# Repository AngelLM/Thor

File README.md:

<h1 align="center">
 <a href="http://thor.angel-lm.com">
    <picture>
      <source height="80" media="(prefers-color-scheme: dark)" srcset="doc/logo_dark.svg">
      
    </picture>
  </a>

 <br>

</h1>
<p align="center">
 <em><b>Thor</b> is an open source, 3D printed, 6 degrees of freedom robotic arm. Designed to be affordable and accessible, Thor is ideal for educational settings, makers, and robotics enthusiasts. With a height of 625mm it has the capacity to lift up to 750g. Its yaw-roll-roll-yaw-roll-yaw configuration is common in industrial manipulators.</em>
</p>

## ✨ Key Features

- 🧩 **Born Open Source**: Designed using open source software such as FreeCAD, KiCAD, GRBL, RRF and ROS.
- 🕊️ **Released Open Source**: All source files published under CC-BY-SA-4.0 license.
- 💰 **Low Cost**: Hardware cost below 350€.
- 📚  **Suitable for education**: Perfect for robotics courses in schools and universities, there are already success cases!
- 🧰 **G-code Controlled**: Uses the same language as 3d printers and CNCs to move.
- 🐳 **ROS2 Integration**: Available implementation using Docker for flexibility.

## 📦 Repository Structure
- `freecad-src` – Source files of 3D models created with FreeCAD
- `mods` – Modified models and improvements to standard models
- `stl` – Printable STL files
- `step` – STEP files

## 🔗 Related Repositories
- [**Thor-ROS**](https://github.com/AngelLM/Thor-ROS): ROS2 & Moveit2 configuration files and packages to work with Thor.
- [**ThorControlPCB**](https://github.com/AngelLM/ThorControlPCB): Source & manufacture files of Arduino Mega shield designed to control Thor.
- [**Asgard**](https://github.com/AngelLM/Asgard): Control software for thor motors with a simple interface.

## 🚀 Getting Started

1. **Read the Documentation**: Comprehensive guides on printing, assembly, electronics, and firmware are available at [thor.angel-lm.com/documentation](http://thor.angel-lm.com/documentation/).
2. **Print the Parts**: Use the STL files in this repository.
3. **Get the Hardware**: Take a look to the [Bill of Materials](http://thor.angel-lm.com/documentation/bom/).
4. **Assemble the Robot**: See [here](http://thor.angel-lm.com/documentation/assembly/) for assembly videos and interactive instructions. 
5. **Assemble & Setup the Electronics**: The [Wiring & Setup](http://thor.angel-lm.com/documentation/electronics/) guide will help you prepare your electronic board and make the hardware connections. 
6. **Install the Firmware**: Depending on which electronics you have chosen, you will have to perform a different firmware configuration. [This page](http://thor.angel-lm.com/documentation/firmware/) explains the steps to follow.
7. **Control the Robot**: Use Asgard to move the robot. [Here](http://thor.angel-lm.com/documentation/control-software/) is how to do it.

## 🧠 Technical Specifications

- **Degrees of Freedom**: 6 (yaw-roll-roll-yaw-roll-yaw).
- **Height Stretched**: 625mm (without end effector).
- **Payload Capacity**: 750g max (including end effector weight).
- **Motors**: Stepper motors.
- **Electronics**: DIY PCB or commercial boards.
- **Transmission**: 3D printed gears, GT2 pulleys and belts.
- **Software**: FreeCAD, KiCAD, GRBL, RRF, ROS2.

## 📚 Additional Resources

- 🌐 **Official Website**: [thor.angel-lm.com](http://thor.angel-lm.com/)
- ❓ **Frequently Asked Questions**: [FAQ](http://thor.angel-lm.com/faq/)
- 💬 **Thor Community Forums**: [Thor Forums](http://thor.angel-lm.com/forums/)
- 💬 **Thor Discord Server**: [Thor Robot Community](https://discord.com/invite/a5dSVqSUK5)

## 🤝 Contributing

Contributions are welcome! If you'd like to improve Thor — whether it's design, documentation, or code — feel free to open an [Issue](https://github.com/AngelLM/Thor/issues) or submit a Pull Request.

## 📜 License

Thor is licensed under the [Creative Commons Attribution-ShareAlike 4.0 International License](https://creativecommons.org/licenses/by-sa/4.0/legalcode). You’re free to use, modify, and distribute this project under its terms.

## 🎥 Videos

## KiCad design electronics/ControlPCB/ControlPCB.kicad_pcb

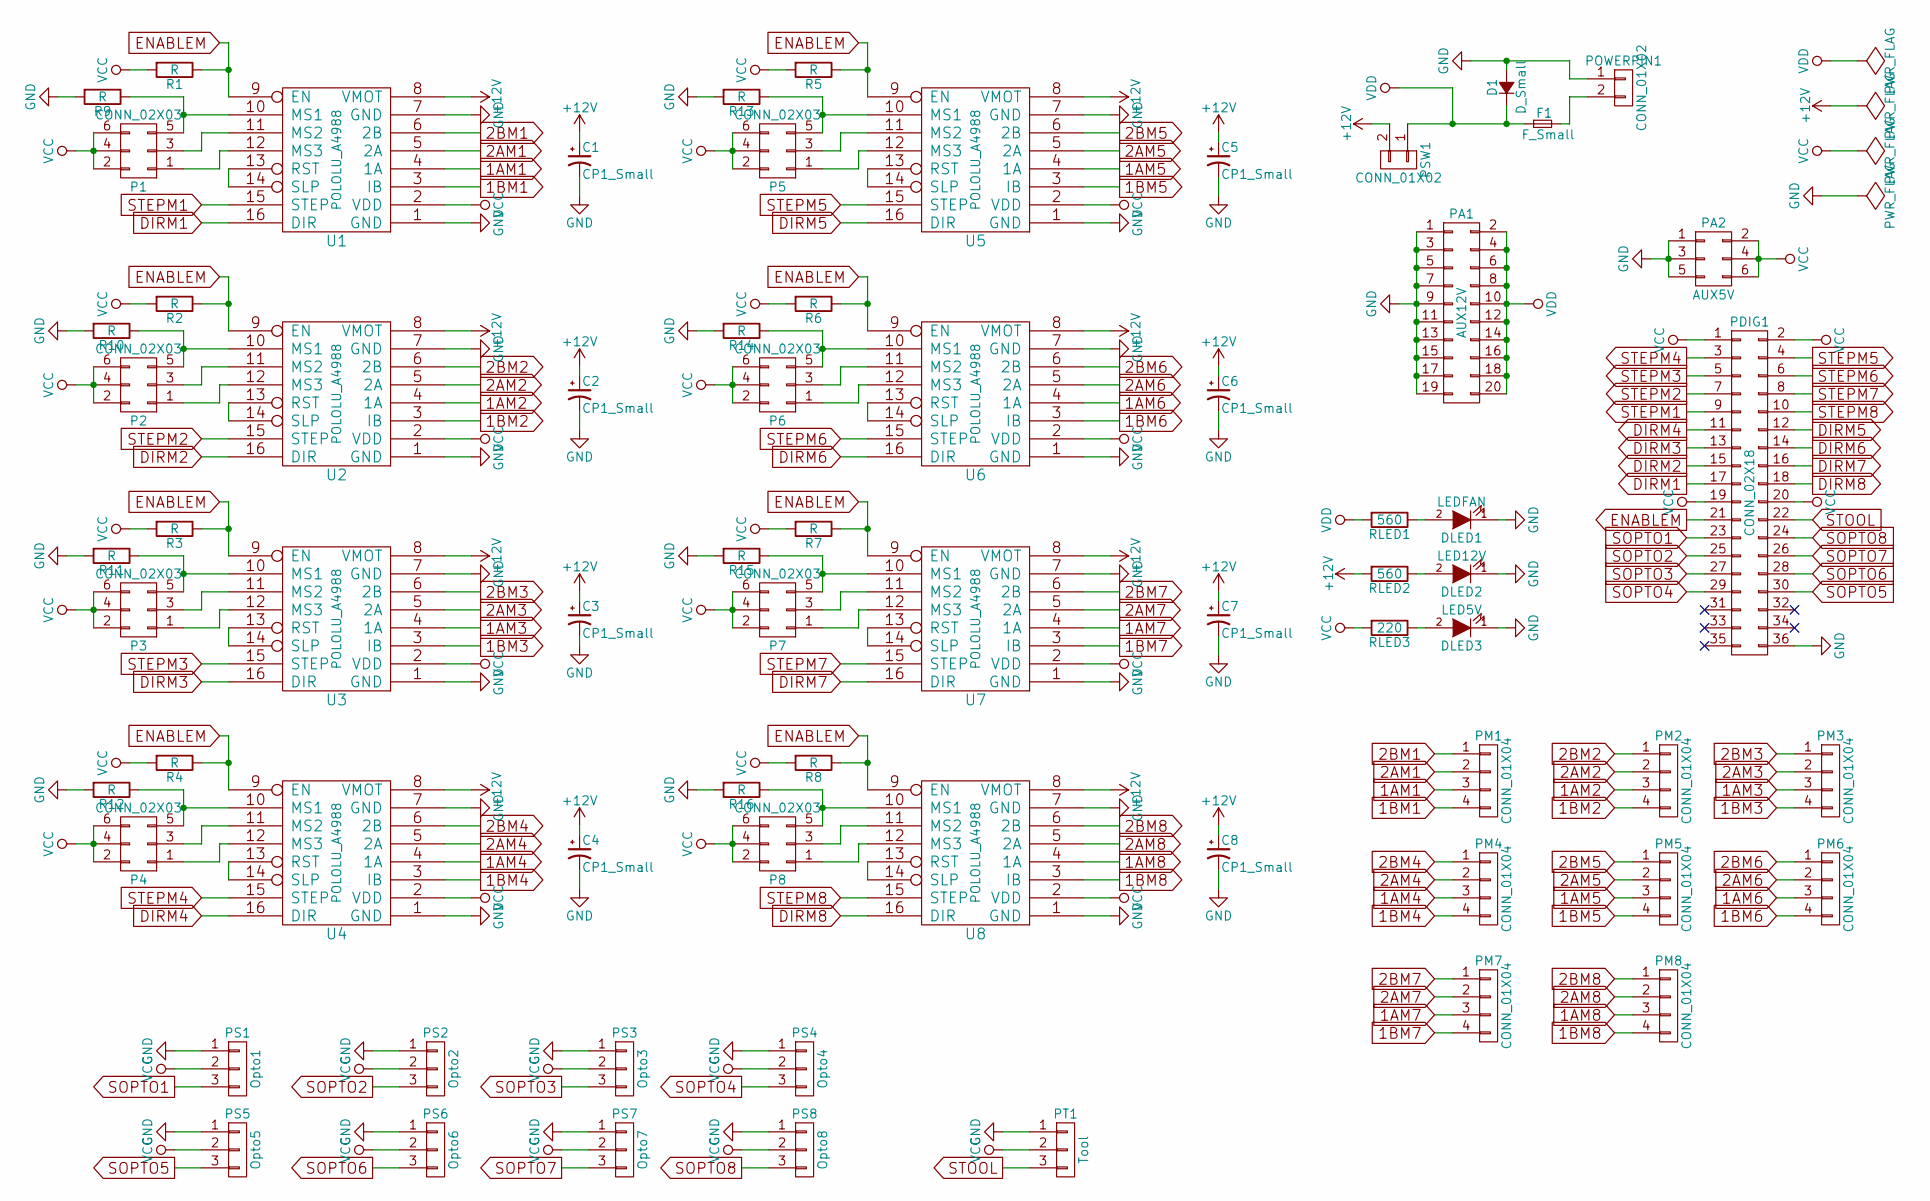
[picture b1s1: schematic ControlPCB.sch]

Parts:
C1, C2, C3, C4, C5, C6, C7, C8: CP1_Small; c_elec_6.3x5.7
D1: D_Small; Diode_DO-35_SOD27_Horizontal_RM10
DLED1: LEDFAN; LED_1206
DLED2: LED12V; LED_1206
DLED3: LED5V; LED_1206
F1: F_Small; BladeFuse-CarType
P1, P2, P3, P4, P5, P6, P7, P8: CONN_02X03; Pin_Header_Straight_2x03
PA1: AUX12V; Pin_Header_Straight_2x10
PA2: AUX5V; Pin_Header_Straight_2x03
PDIG1: CONN_02X18; Pin_Header_Straight_2x18
PM1, PM2, PM3, PM4, PM5, PM6, PM7, PM8: CONN_01X04; Pin_Header_Straight_1x04
POWERPIN1: CONN_01X02; Pin_Header_Straight_1x02
PS1: Opto1; Pin_Header_Straight_1x03
PS2: Opto2; Pin_Header_Straight_1x03
PS3: Opto3; Pin_Header_Straight_1x03
PS4: Opto4; Pin_Header_Straight_1x03
PS5: Opto5; Pin_Header_Straight_1x03
PS6: Opto6; Pin_Header_Straight_1x03
PS7: Opto7; Pin_Header_Straight_1x03
PS8: Opto8; Pin_Header_Straight_1x03
PSW1: CONN_01X02; Pin_Header_Straight_1x02
PT1: Tool; Pin_Header_Straight_1x03
R1, R2, R3, R4, R5, R6, R7, R8, R9, R10, R11, R12, R13, R14, R15, R16: R; R_1206_HandSoldering
RLED1, RLED2: 560; R_1206_HandSoldering
RLED3: 220; R_1206_HandSoldering
U1, U2, U3, U4, U5, U6, U7, U8: POLOLU_A4988; SWDIP8_.6W

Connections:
1AM1: PM1.3, U1.4 (1A)
1AM2: PM2.3, U2.4 (1A)
1AM3: PM3.3, U3.4 (1A)
1AM4: PM4.3, U4.4 (1A)
1AM5: PM5.3, U5.4 (1A)
1AM6: PM6.3, U6.4 (1A)
1AM7: PM7.3, U7.4 (1A)
1AM8: PM8.3, U8.4 (1A)
1BM1: PM1.4, U1.3 (IB)
1BM2: PM2.4, U2.3 (IB)
1BM3: PM3.4, U3.3 (IB)
1BM4: PM4.4, U4.3 (IB)
1BM5: PM5.4, U5.3 (IB)
1BM6: PM6.4, U6.3 (IB)
1BM7: PM7.4, U7.3 (IB)
1BM8: PM8.4, U8.3 (IB)
2AM1: PM1.2, U1.5 (2A)
2AM2: PM2.2, U2.5 (2A)
2AM3: PM3.2, U3.5 (2A)
2AM4: PM4.2, U4.5 (2A)
2AM5: PM5.2, U5.5 (2A)
2AM6: PM6.2, U6.5 (2A)
2AM7: PM7.2, U7.5 (2A)
2AM8: PM8.2, U8.5 (2A)
2BM1: PM1.1, U1.6 (2B)
2BM2: PM2.1, U2.6 (2B)
2BM3: PM3.1, U3.6 (2B)
2BM4: PM4.1, U4.6 (2B)
2BM5: PM5.1, U5.6 (2B)
2BM6: PM6.1, U6.6 (2B)
2BM7: PM7.1, U7.6 (2B)
2BM8: PM8.1, U8.6 (2B)
+12V: C1.1, C2.1, C3.1, C4.1, C5.1, C6.1, C7.1, C8.1, PSW1.2, RLED2.2, U1.8 (VMOT), U2.8 (VMOT), U3.8 (VMOT), U4.8 (VMOT), U5.8 (VMOT), U6.8 (VMOT), U7.8 (VMOT), U8.8 (VMOT)
DIRM1: PDIG1.17, U1.16 (DIR)
DIRM2: PDIG1.15, U2.16 (DIR)
DIRM3: PDIG1.13, U3.16 (DIR)
DIRM4: PDIG1.11, U4.16 (DIR)
DIRM5: PDIG1.12, U5.16 (DIR)
DIRM6: PDIG1.14, U6.16 (DIR)
DIRM7: PDIG1.16, U7.16 (DIR)
DIRM8: PDIG1.18, U8.16 (DIR)
ENABLEM: PDIG1.21, R1.1, R2.1, R3.1, R4.1, R5.1, R6.1, R7.1, R8.1, U1.9 (EN), U2.9 (EN), U3.9 (EN), U4.9 (EN), U5.9 (EN), U6.9 (EN), U7.9 (EN), U8.9 (EN)
GND: C1.2, C2.2, C3.2, C4.2, C5.2, C6.2, C7.2, C8.2, D1.2 (A), DLED1.1 (K), DLED2.1 (K), DLED3.1 (K), PA1.1, PA1.3, PA1.5, PA1.7, PA1.9, PA1.11, PA1.13, PA1.15, PA1.17, PA1.19, PA2.1, PA2.3, PA2.5, PDIG1.36, POWERPIN1.1, PS1.1, PS2.1, PS3.1, PS4.1, PS5.1, PS6.1, PS7.1, PS8.1, PT1.1, R9.2, R10.2, R11.2, R12.2, R13.2, R14.2, R15.2, R16.2, U1.1 (GND), U1.7 (GND), U2.1 (GND), U2.7 (GND), U3.1 (GND), U3.7 (GND), U4.1 (GND), U4.7 (GND), U5.1 (GND), U5.7 (GND), U6.1 (GND), U6.7 (GND), U7.1 (GND), U7.7 (GND), U8.1 (GND), U8.7 (GND)
unnamed: DLED1.2 (A), RLED1.1
unnamed: DLED2.2 (A), RLED2.1
unnamed: DLED3.2 (A), RLED3.1
unnamed: F1.2, POWERPIN1.2
unnamed: P1.1, U1.12 (MS3)
unnamed: P1.3, U1.11 (MS2)
unnamed: P1.5, R9.1, U1.10 (MS1)
unnamed: P2.1, U2.12 (MS3)
unnamed: P2.3, U2.11 (MS2)
unnamed: P2.5, R10.1, U2.10 (MS1)
unnamed: P3.1, U3.12 (MS3)
unnamed: P3.3, U3.11 (MS2)
unnamed: P3.5, R11.1, U3.10 (MS1)
unnamed: P4.1, U4.12 (MS3)
unnamed: P4.3, U4.11 (MS2)
unnamed: P4.5, R12.1, U4.10 (MS1)
unnamed: P5.1, U5.12 (MS3)
unnamed: P5.3, U5.11 (MS2)
unnamed: P5.5, R13.1, U5.10 (MS1)
unnamed: P6.1, U6.12 (MS3)
unnamed: P6.3, U6.11 (MS2)
unnamed: P6.5, R14.1, U6.10 (MS1)
unnamed: P7.1, U7.12 (MS3)
unnamed: P7.3, U7.11 (MS2)
unnamed: P7.5, R15.1, U7.10 (MS1)
unnamed: P8.1, U8.12 (MS3)
unnamed: P8.3, U8.11 (MS2)
unnamed: P8.5, R16.1, U8.10 (MS1)
unnamed: U1.13 (RST), U1.14 (SLP)
unnamed: U2.13 (RST), U2.14 (SLP)
unnamed: U3.13 (RST), U3.14 (SLP)
unnamed: U4.13 (RST), U4.14 (SLP)
unnamed: U5.13 (RST), U5.14 (SLP)
unnamed: U6.13 (RST), U6.14 (SLP)
unnamed: U7.13 (RST), U7.14 (SLP)
unnamed: U8.13 (RST), U8.14 (SLP)
SOPTO1: PDIG1.23, PS1.3
SOPTO2: PDIG1.25, PS2.3
SOPTO3: PDIG1.27, PS3.3
SOPTO4: PDIG1.29, PS4.3
SOPTO5: PDIG1.30, PS5.3
SOPTO6: PDIG1.28, PS6.3
SOPTO7: PDIG1.26, PS7.3
SOPTO8: PDIG1.24, PS8.3
STEPM1: PDIG1.9, U1.15 (STEP)
STEPM2: PDIG1.7, U2.15 (STEP)
STEPM3: PDIG1.5, U3.15 (STEP)
STEPM4: PDIG1.3, U4.15 (STEP)
STEPM5: PDIG1.4, U5.15 (STEP)
STEPM6: PDIG1.6, U6.15 (STEP)
STEPM7: PDIG1.8, U7.15 (STEP)
STEPM8: PDIG1.10, U8.15 (STEP)
STOOL: PDIG1.22, PT1.3
VCC: P1.2, P1.4, P1.6, P2.2, P2.4, P2.6, P3.2, P3.4, P3.6, P4.2, P4.4, P4.6, P5.2, P5.4, P5.6, P6.2, P6.4, P6.6, P7.2, P7.4, P7.6, P8.2, P8.4, P8.6, PA2.2, PA2.4, PA2.6, PDIG1.1, PDIG1.2, PDIG1.19, PDIG1.20, PS1.2, PS2.2, PS3.2, PS4.2, PS5.2, PS6.2, PS7.2, PS8.2, PT1.2, R1.2, R2.2, R3.2, R4.2, R5.2, R6.2, R7.2, R8.2, RLED3.2, U1.2 (VDD), U2.2 (VDD), U3.2 (VDD), U4.2 (VDD), U5.2 (VDD), U6.2 (VDD), U7.2 (VDD), U8.2 (VDD)
VDD: D1.1 (K), F1.1, PA1.2, PA1.4, PA1.6, PA1.8, PA1.10, PA1.12, PA1.14, PA1.16, PA1.18, PA1.20, PSW1.1, RLED1.2

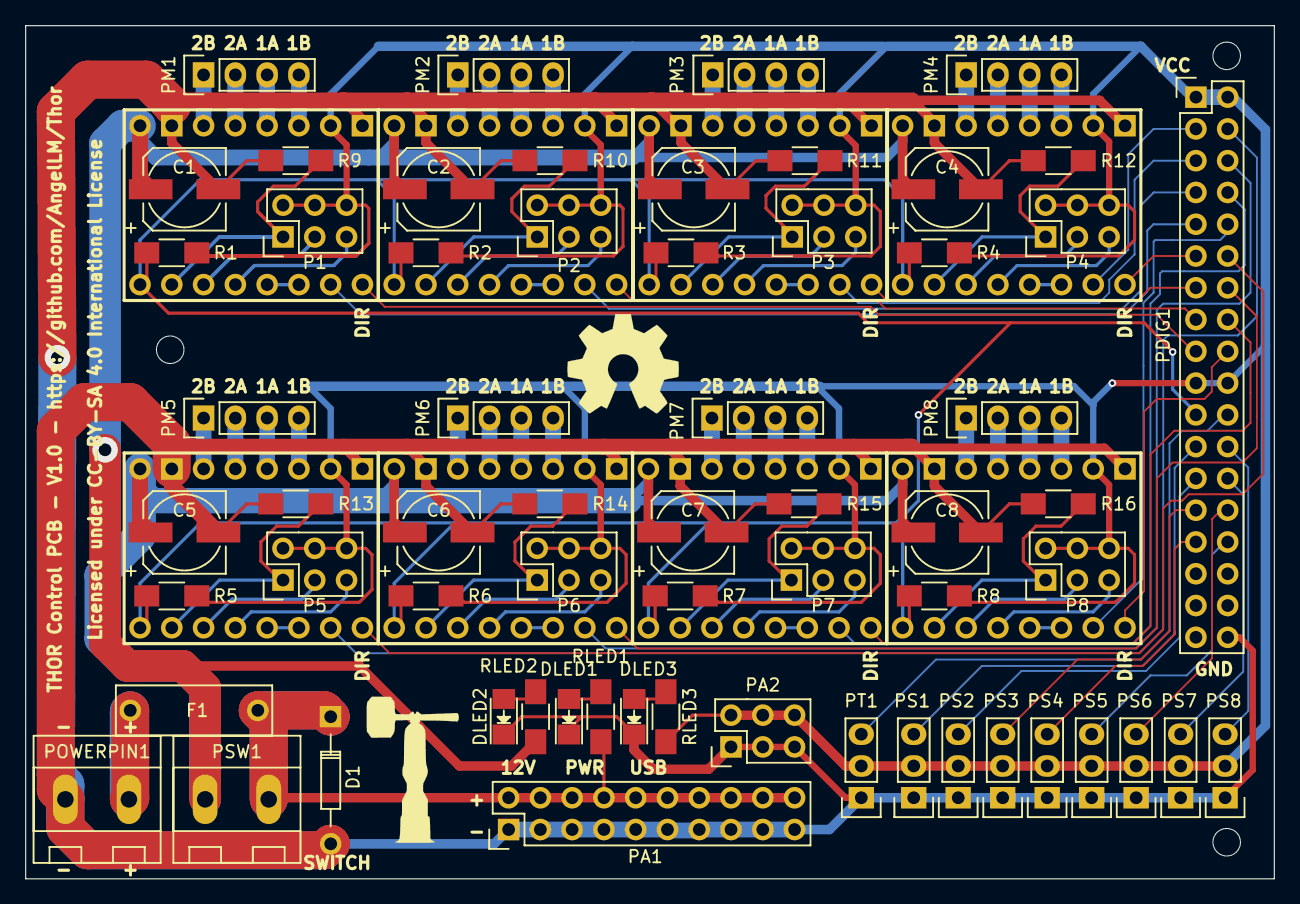
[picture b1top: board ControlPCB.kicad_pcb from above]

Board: 2 copper layers, 99.8 x 68.2 mm, 70 parts (0 on the bottom side), 98 nets.

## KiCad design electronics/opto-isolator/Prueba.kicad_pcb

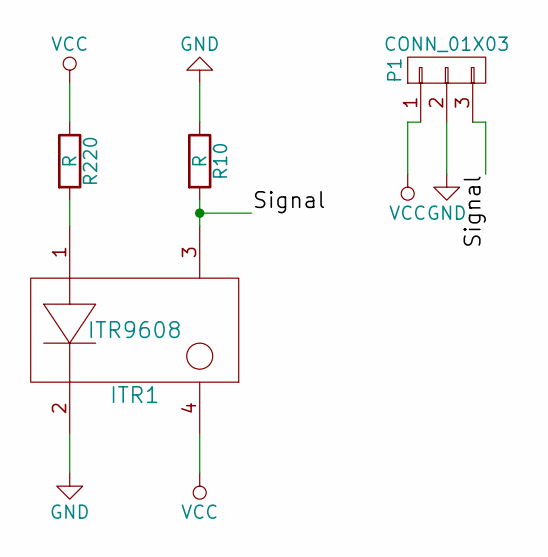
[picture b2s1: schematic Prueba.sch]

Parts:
ITR1: ITR9608
P1: CONN_01X03; Pin_Header_Angled_1x03
R10, R220: R; Resistor_Horizontal_RM10mm

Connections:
/Signal: ITR1.3, P1.3, R10.2
GND: ITR1.2, P1.2, R10.1
unnamed: ITR1.1, R220.2
VCC: ITR1.4, P1.1, R220.1

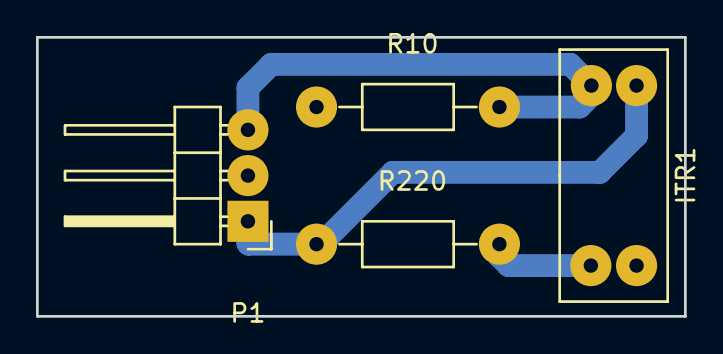
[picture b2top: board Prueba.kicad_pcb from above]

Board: 2 copper layers, 36.0 x 15.5 mm, 4 parts (0 on the bottom side), 4 nets.

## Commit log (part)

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2015-04-23 Added FreeCAD files, Readme and By-sa image.
2015-04-26 Base fixed
2015-04-26 Base Bearing Anchors fixed, Articulation 1 and Articulation 1 anchors fixed
2015-04-26 Base motor fix1 applied, Base motor fix2 applied, articulation 1 fixed, screenshots added
2015-04-27 .step and .stl base files added
2015-04-27 Articulation 2&3 motors added. GT2 Motor pulley added.
2015-04-28 2x Articulation 1 body added. Testing shapes.
2015-04-28 2x Articulation 1 body added. Testing shapes. Updated
2015-04-29 Articulation 2 Body added
2015-05-03 GT2 Pulley Big Added, Pieces updated
2015-05-11 New base model added
2015-05-13 Base updated
2015-05-18 Articulation 1 body udated
2015-05-21 Transm Pulley Open Belt changed. Nema 14 motor datasheet added.
2015-05-21 Transm pulley for Articulation 2 added
2015-05-24 Base & Articulation 1 modified
2015-05-26 Articulation 1 modified
2015-05-26 Base & Articulation 1 updated
2015-05-26 Base & Articulation 1 modified. Old .stl files removed.
2015-05-30 Articulation normal gears converted to helical gears
2015-06-01 Articulation 1 motor fix modified
2015-06-01 Stl files added. Assembly pictures added.
2015-06-01 Gcode files added
2015-06-01 Readme Gcode added
2015-06-07 Articulation 1 Body updated
2015-06-13 Articulation 1 and 2 modified
2015-06-19 Articulation 1 Body modified. Articulation 2 Modified.
2015-06-19 Articulation2 Cover Added
2015-06-22 Articulation 2 modified
2015-06-22 Art2 Support added, Art1 fix added
2015-07-08 Bearings fixed. Articulation 5&6 added. Articulation 4 modified. Articulation 2 & 3 updated.
2015-07-08 File Thor.fcstd.328c8f03-1e98-43c8-bf82-f552401c5301 removed
2015-07-09 Some files and LICENSE updated
2015-07-21 Articulation 4,5,6 updated
2015-07-22 Articulation 4, 5 & 6 modified
2015-07-27 Some bugs fixed
2015-08-01 Some errors fixed
2015-08-02 Added Window to Art2 Body B, Fixed Window Art2 Body A
2015-08-02 List of materials added
2015-08-02 Removed extra files
2015-08-02 fcstd1 file removed
2015-08-03 Art2 & Art3 Updated, gitignore added
2015-08-03 Art3 & Art4 modified
2015-08-05 gcode, step and stl folders & files removed
2015-08-10 Some parts updated, stl added
2015-08-11 Art2-BodyB modified. New stl files
2015-08-12 Art2 BodyA modified & stl added
2015-08-12 Art2 BodyA modified, stl files added
2015-08-12 Bearing housing fixed
2015-08-13 stl of fixed part generated, art1 body fixed
2015-08-13 New gears, fixed art5&6 parts
2015-08-13 Art5&6 fixed, window added
2015-08-14 some stl added
2015-08-16 Base error fixed
2015-08-26 pruebas & update
2015-08-26 Art56 fix
2015-08-31 More fixes
2015-08-31 light update
2015-09-06 Torque measures
2015-12-02 prueba tensor gcode added
2015-12-02 FreeCAD model updated: Articulation1 parts fixed
2015-12-02 FreeCAD model updated: Articulation2 parts fixed
2015-12-02 FreeCAD model updated: Articulation3 parts fixed
2015-12-02 FreeCAD model updated: Articulation4 parts fixed
2015-12-02 extra file removed
2015-12-02 STL folder removed
2015-12-02 gcode folder removed
2015-12-02 Gallery folder & pictures deleted
2015-12-03 FreeCAD model updated: Articulation5&6 parts fixed
2015-12-03 FreeCAD model general update
2015-12-03 FreeCAD model updated: Articulation 2 tensioner fixed
2015-12-04 FreeCAD model updated, picture added
2015-12-09 Images for documentatio added
2015-12-09 Scaled some images
2015-12-14 Control scripts added
2015-12-15 Separated FreeCAD files uploaded, control script uploaded
2015-12-15 Control script upgraded
2015-12-15 Control script updated
2015-12-16 Articulation 2 images added
2015-12-17 Added Blender files
2015-12-17 FreeCAD motor variation file updated
2015-12-17 Blender files updated
2015-12-18 FreeCAD and Blender files updated
2015-12-21 Tensioners & Body A updated
2015-12-22 FreeCAD Files updated, added images for wiki documentation
2015-12-22 Image name changed
2015-12-22 Articulation 4 images added
2015-12-22 Art4-BodyTop images scaled
2015-12-22 Home marks added to FreeCAD files
2015-12-24 Thor-Base.fcstd updated
2015-12-24 Thor-Art1.fcstd updated
2015-12-24 Thor-Art2.fcstd updated
2015-12-24 Thor-Art3.fcstd updated
2015-12-24 FreeCAD files general update
2015-12-28 FreeCAD Files updated
2015-12-29 FreeCAD Files & firmware update
2015-12-30 New FreeCAD Files
2016-01-07 Art1Body updated
2016-01-08 FreeCAD file updated
2016-01-11 Renferences fix
2016-01-11 Art2 updated
2016-01-12 Art3 updated
2016-01-12 Art4 added
2016-01-13 Art4 modified, Art56 parts added
2016-01-13 Tolerances added
2016-01-13 Art56 Gears added
2016-01-14 Model updated
2016-01-14 3D Model modified - optoisolators
2016-01-17 KiCad File of Optoisolator PCB added
2016-01-20 Electronics update
2016-01-27 tolerances update
2016-01-27 Old files deleted, main file renamed
2016-01-27 Base restyled
2016-02-01 Art 1,2,3 & 4 modified to fix the Opto-isolator PCB
2016-02-03 Some bugs fixed, added Art5 endstop
2016-02-04 Art4Body part modified
2016-02-24 Art3 Pulley Fixed
2016-02-24 Bearing Art4 Fixed
2016-02-24 Main FreeCAD File Splitted
2016-02-29 Art2 BodyAWindow Fixed
2016-02-29 BaseBot fixed
2016-02-29 Art2BodyACover1 fixed
2016-02-29 Art1Body fix
2016-03-02 ControlPCB Kicad project added
2016-03-03 ControlPCB Kicad project update
2016-03-03 ControlPCB update
2016-03-04 ControlPCB updated, gerber and drills files added
2016-03-07 Art4BearingRing fixed
2016-03-07 ThorAssembly added
2016-03-11 BQLabs web update
2016-03-11 Library update
2016-03-11 Removed duplicated files
2016-03-14 Art3Pulley Fixed
2016-03-14 Added Assembly (printed parts)
2016-03-15 minor update
2016-03-16 Art2MotorGearFixed
2016-03-16 Assembly minor update. Art1OptoFixFixed. BaseBot Fixed
2016-03-17 Art1Bot, Art1OptoFix and Assembly Updated
2016-03-17 Assembly updated
2016-03-21 Some parts fixed, assembly updated!
2016-03-22 Assembly update, some parts fixed
2016-03-22 Assembly almost done, Art2MotorGear and Art56CoverRing Fixed
2016-03-29 Added Tensioner freecad files, Assembly updated
2016-03-29 Assembly fixed
2016-03-29 First try of Animation
2016-05-08 Animation Part1 & Part2 added
2016-05-09 Animation Part3
2016-05-09 Part3 Update
2016-05-10 Added micro-endstop on Assembly file, Added AnimationPart4
2016-05-10 Animation Part5 Added
2016-05-15 Animation 5 hotfix
2016-05-17 Blender files deleted. Them will be moved to a new branch
2016-05-17 Old images removed, updated locations of other pictures
2016-05-17 Firmware files deleted. Them will be moved to a new branch
2016-05-17 Old Datasheets removed
2016-05-17 Test folder removed
2016-05-17 Source files reorganized
2016-05-17 Readme update
2016-05-30 animation hotfix
2016-07-25 STL files added
2016-07-25 Art4Body file renamed
2016-07-27 ReadmeUpdate
2016-08-03 Removed misplaced stl
2016-08-03 LOM added
2016-08-03 LOM fixed
2016-08-11 LOM Updated
2016-09-29 Some printed parts modified to allow airflow
2016-10-19 Added 40mmfan support
2016-10-25 Art1Top modified - issue#29
2016-11-07 Assembly updated, issue solved, ready to merge
2016-11-07 Art4OptoFix STL file added
2016-11-17 changes added
2016-11-26 PCB update
2016-11-26 update2
2016-11-27 ControlPCB before square
2016-11-30 mistakes were made
2016-12-07 ControlPCB silkscreen cleaned!
2016-12-08 Gerber files uploaded
2016-12-19 KiCAD 3D models paths modified
2016-12-21 Added Art4 3D model modified, remixed from Danny-VdH modifications
2016-12-21 Added Base 3D model modified, remixed from Ctrl-Alt-Dude modifications
2016-12-21 Added Art4 3D model modified, remixed from @Danny-VdH modifications
2016-12-21 Repository well sorted
2016-12-21 Readme hotfix
2016-12-30 Art4BearingPlug Added
2017-01-10 Step files added
2017-01-14 FAQ added
2017-01-14 FAQ hotfix
2017-01-15 FAQ & README updated
2017-01-16 List of Thor builders added
2017-01-16 Added modifications, still working on them
2017-02-14 New Thor Builders added, FAQ updated
2017-03-15 Including Danny 3 STL files for the Base
2017-03-22 Splitted Art1Bot in two parts
2017-03-31 ThorBuilders List updated!
2017-04-02 Motors updates according to Thor+
2017-04-02 Initial Step files Removed
2017-04-02 Some images from doc were removed
2017-04-02 Some changes in visualization
2017-04-02 Starting the Preassembly for the splitted 2 parts
2017-04-02 Starting to modifing the model according tho Thor+
2017-04-02 Removing the old .gcodes
2017-04-02 Removing the auxiliary files generated by skeinforge
2017-04-02 organizing the folder
2017-04-02 organizing the folder in subfolders
2017-04-02 Accidentally erased, sorry...
2017-04-02 Freecad file for Art1BodyP2 was started to be modified
2017-04-02 openscad folder was created to store the modified STL files from Thor+
2017-04-02 adding .stl file to stl folder
2017-04-02 Art1 Files removed
2017-04-02 Base Files removed
2017-04-02 Fixed permissions on the images
2017-04-02 location for the image was fixed
2017-04-10 Thor Builders Addition
2017-04-11 Fixed header markup
2017-04-11 Updated firmware link
    Matching the format of the other list links.
2017-04-11 Created builder table
    Sorted by project state
2017-04-11 Improved language
2017-04-11 Grammar tweaks
2017-04-11 Converted lists to tables
    Should make things easier to read
2017-04-11 the head's screw was made bigger
2017-04-11 add the gcode for Art1Body_P3
2017-04-12 added last images of Art1Body_P3
2017-04-12 started to add gcodes for Art2
2017-04-12 added Art2BodyA_P2 gcode
2017-04-13 gcode Art2BodyACover added
2017-04-15 Art2BodyACover_P2 gcode added
2017-04-15 .directory files added
2017-04-16 Art2Body_P1 gcode added
2017-04-18 Art2Union gcode added
2017-04-18 .directory files changed
2017-04-22 Wire diagram addedfor v1.0
2017-04-24 WireDiagram Enhanced
2017-04-25 Logo wiki image added
2017-04-25 Info moved to wiki
2017-05-04 Electronics schematics
2017-08-08 STL of full articulations added
2017-08-16 Art3 & Base adapted
2017-08-16 Files redesigned, assembly and step files left
2017-08-17 Commercial Sensors redesign done
2018-01-09 Color update
2018-01-10 GripperActiveArmFix & griper STL files generated
2018-01-10 Yeah b@#ch! Magnets!
2018-01-15 Monday update
2018-01-15 filenames fix
2018-01-25 Art56, Gripper and BaseBoxBody modified
2018-02-12 Fixed LICENSE error
    Since the first readme commit I wrote that every file included in this repository is licensed under CC-BY-SA 4.0 License.
    The LICENSE file until now was wrong.
    This commit fix that error
2018-07-04 solved
2018-07-04 Ups, license image restored!
2018-07-15 BaseBox fixed, Assembly updated
2021-01-15 make the gap of body1 for stepper shaft wider
2021-08-02 Pull Request Fix
2021-08-02 some deprecated freecad folder removed
2021-08-02 Removed deprecated mods
2021-08-02 Removed deprecated files
2021-08-02 Added FreeCAD files of Thor V2.1 Redesign
2021-08-02 Added STL files of Thor V2.1 Redesign
2021-08-02 Added STEP files of Thor V2.1 Redesign
2021-08-08 Updated Readme to Thor v2.1
2021-09-23 Hotfix Art1Body steppers housing
2021-09-23 2nd Hotfix Art1Body steppers housing
2022-05-08 Deleted Art4OptoDisk.stl
    Looks like it's a duplicate of `Art4Optodisk.stl` (lowercase 'd')
2022-08-02 Added SuctionCupToolHolder FreeCAD, STL and STEP files
    This part is designed to hold a suction cup tool to be used as an end effector.
2022-08-02 Added SupportRoller part files
    Place a pair of roller bearings into this part with some M5 nuts and bolts and place under Art2 on the side where the joint tends to sag.
2022-08-02 Added Art4MotorShim part files
    I used this part to move the Art4 motor closer to the Art4TransmissionColumn, closing the gap between the gears and reducing the backlash.
2022-08-02 Added Art2BodyUnion_mod part files. Increases range of motion Art3.
    Easy to replace, this part will give you approximately 11 extra degrees of range of motion in Art3.
2022-08-02 Fix typos
2023-01-11 Fixed BaseBot.step
2023-09-14 Modified Art4BearingRing for tighter fit with 5.98mm ball bearings from AliExpress
2023-12-07 Added se1exin mod, moved to mods new folder
2023-12-28 DIY servo connector replaced by GX12
2023-12-31 GX12 replaced with M8 connector
2024-01-01 Art4Body and Art56SmallGear modified to ease assembly
2024-01-02 Modification to ease the semidifferential assembly
2024-02-11 Updated STL & STEP files of Art4Body and Art56SmallGear
2024-09-07 add servo connector for attaching gripper

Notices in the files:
electronics/ControlPCB/ControlPCB.kicad_pcb:
Licensed under CC-BY-SA 4.0 International License
